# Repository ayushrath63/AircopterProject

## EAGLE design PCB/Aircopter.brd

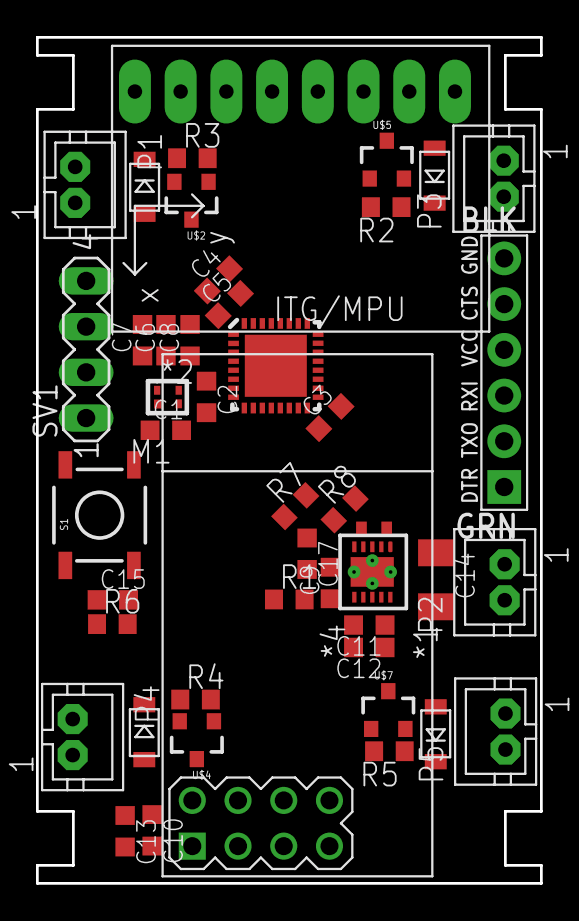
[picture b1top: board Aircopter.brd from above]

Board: 2 copper layers, 28.0 x 47.0 mm, 46 parts (0 on the bottom side), 31 nets, no tracks yet.

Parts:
*1: STM32L432KCU6; QFN32_5X5MM
*2: DSC6001CI1A-008.0000T; VFLGA4
*4: TPS63001DRCRTPS63001DRCR_VSON10; VSON10
C1, C3, C4, C7, C9, C10, C15: 100n; C0603K
C2: 10p\; C0603K
C5: 4.7u; C0603K
C6: 10n; C0603K
C8: 1u; C0603K
C11, C12, C13, C17: 10u; C0603K
C14: 100u; C1206K
J1: FTDI_DEVICE; FTDI_DEVICE_SIDE
M1: WIRELESS-NRF24L01
P1, P2, P3, P4, P5: JST-PH2
R1, R2, R3, R4, R5, R6, R7, R8: 10k; R0603
S1: TACTILE-SWITCH-SMD
SV1: MA04-1
U1: GY-521MPU6050; GY-521
U$1, U$3, U$6, U$8: 1N4001; MINI2-F3-B
U$2, U$4, U$5, U$7: IRLML6244TRPBF; SOT23-3
U$9: 1.5u; L-0603

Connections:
+3V3: *1.1, *1.5, *1.17, *2.1, *2.4, *4.1, *4.10, C1.1, C3.1, C4.1, C5.1, C6.1, C7.1, C8.1, C10.1, C11.1, C12.1, C13.1, J1.P$4, M1.2, R6.2, U1.VCC
BATSENSE: *1.15, R7.2, R8.1
CTS: *1.21, J1.P$5
GND: *1.16, *1.32, *1.EPAD, *2.2, *4.3, *4.9, *4.EPAD, C1.2, C2.2, C6.2, C7.2, C8.2, C9.2, C10.2, C11.2, C12.2, C13.2, C14.2, C15.2, C17.2, J1.P$6, M1.1, P2.2, R2.1, R3.1, R4.1, R5.1, R8.2, S1.3, SV1.3, U1.ADO, U1.GND, U$2.2, U$4.2, U$5.2, U$7.2
MISO: *1.12, M1.7
MOSI: *1.13, M1.6
MOTOR1: *1.18, R2.2, U$5.1
MOTOR2: *1.7, R3.2, U$2.1
MOTOR3: *1.8, R4.2, U$4.1
MOTOR4: *1.9, R5.2, U$7.1
unnamed: P3.1, U$1.POS, U$5.3
unnamed: *4.4, U$9.P$2
unnamed: P1.1, U$2.3, U$3.POS
unnamed: *4.2, U$9.P$1
unnamed: *4.6, *4.7, *4.8, C9.1, R1.2
unnamed: P4.1, U$4.3, U$6.POS
unnamed: P5.1, U$7.3, U$8.POS
unnamed: C3.2, C4.2, C5.2
NRST: *1.4, C15.1, R6.1, S1.1, SV1.1
NSS: *1.10, M1.4
OSC: *1.6, *2.3, C2.1
RADIO_CE: *1.14, M1.3
RTS: *1.22, J1.P$1
RX: *1.20, J1.P$3
SCK: *1.11, M1.5
SCL: *1.29, U1.SCL
SDA: *1.30, U1.SDA
SWCLK: *1.24, SV1.4
SWDIO: *1.23, SV1.2
TX: *1.19, J1.P$2
V+: *4.5, C14.1, C17.1, P1.2, P2.1, P3.2, P4.2, P5.2, R1.1, R7.1, U$1.NEG, U$3.NEG, U$6.NEG, U$8.NEG

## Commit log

2018-10-23 Complete checkpoint 1-3 of lab 1
2018-10-23 Removed .gitignore
2018-10-23 Update LED blick frequency
2018-10-23 test git user settings
2018-10-26 Added RX and TX code
2018-10-26 Update RX/TX code
2018-10-26 Fixed RX/TX and added RX & TX targets to makefile
2018-10-29 Testing checkpoint 5
2018-10-30 Fix TX/RX issues
2018-10-30 Random LED selected
2018-10-30 Finish Llama or Duck
2018-11-02 Finish Lab 2
2018-11-02 Update motor control schematic
2018-11-07 Add sensor fusion lab
2018-11-09 Add sensor fusion checkpoint 1
2018-11-09 Data ready not working
2018-11-10 Implement raw_read to get IMU data
2018-11-12 Add Accelerometer orientation tracking
2018-11-13 Add visualizer for accelerometer data
2018-11-13 Increase visualizer update frequency
2018-11-16 Initial gyro reading as quaternion
2018-11-16 Combination filter added, visualizer testing
2018-11-16 Update main.cpp
    Working combination code
2018-11-26 Added Schematic + Library
2018-11-26 Update Schematic
2018-11-28 Update Sch
2018-11-28 Fixed pin map on TPS63001DRCR
2018-11-28 Fixed pin connection on TPS63001DRCR
2018-11-28 Laid out voltage regular subcircuit
2018-11-29 Voltage regulator and battery subcircuit
2018-11-29 Finish Schematic
2019-01-13 Including Jesse's updates to resistor values
2019-01-28 Added initial PCB
2019-01-29 Rearranging board for cleanup
2019-01-31 Mid-design review PCB updates
